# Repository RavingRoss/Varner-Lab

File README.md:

# Current Projects
## SiPMT revA/B:
Includes work on a PCB upgrade to give inputs for a LASER using pogo-pins to activate the given 8 CH ASIC IC chip. 

---

## Waveforms:
Performed testing using dummy data taken from the TOP boardstack in the lab, the waveforms are evenly distributed and plotted.

---

## TOP-BS:
Data taken from the TOP boardstack in Varner lab, testing the 64 SiPM PCB using PCIE40 and KLM VME at UH. Includes advanced version of waveforms parsing script and BS cooling plate upgrades. 

---

## HLS4ML:
This is a project from PHYS 476L which uses the Nexys Video FPGA board for implementation. A keras NN model takes waveform data and predicts the distribution using the mean, sigma, pedestal, and height of the event. This model is then put onto the FPGA by converting it to C using hls4ml. Vitis-HLS is then used to make a Vivado project to implement onto the FPGA.

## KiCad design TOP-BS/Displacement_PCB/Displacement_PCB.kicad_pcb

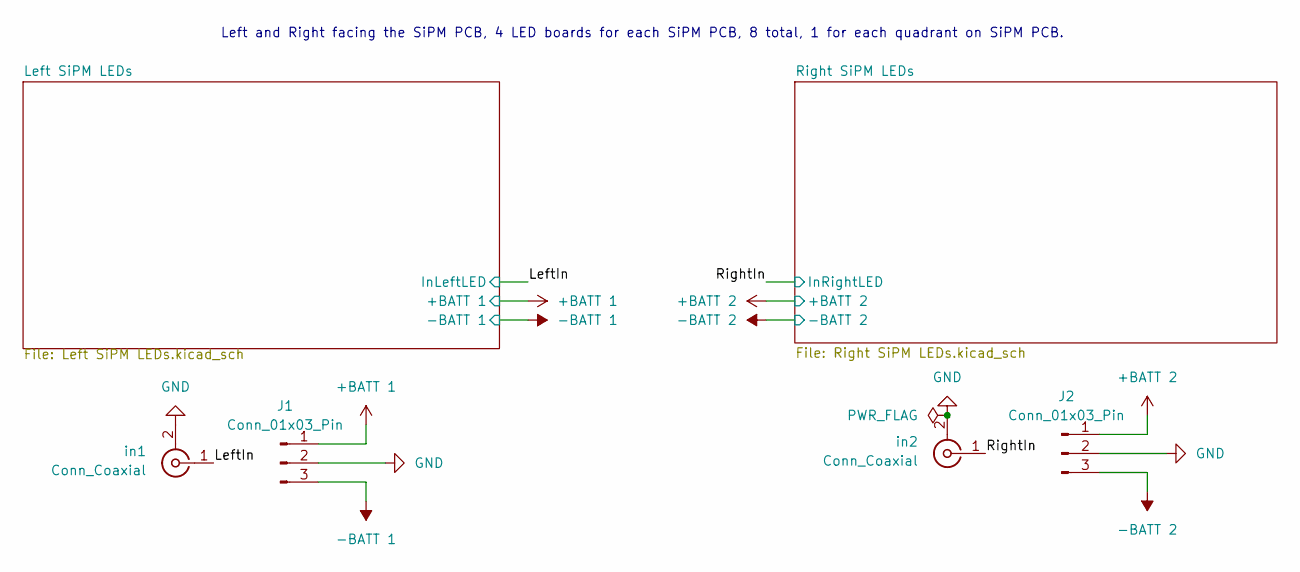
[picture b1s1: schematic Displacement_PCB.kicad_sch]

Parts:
J1, J2: Conn_01x03_Pin; molex-mini-fit-jr-3pos-right-angle-or-16AWG
in1, in2: Conn_Coaxial; MMCX_Molex_73415-1471_Vertical

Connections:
+BATT 1: J1.1; also elsewhere on the board
+BATT 2: J2.1; also elsewhere on the board
-BATT 1: J1.3; also elsewhere on the board
-BATT 2: J2.3; also elsewhere on the board
/LeftIn: in1.1 (In); also elsewhere on the board
/RightIn: in2.1 (In); also elsewhere on the board
GND: J1.2, J2.2, in1.2 (Ext), in2.2 (Ext); also elsewhere on the board

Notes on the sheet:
Left and Right facing the SiPM PCB, 4 LED boards for each SiPM PCB, 8 total, 1 for each quadrant on SiPM PCB.

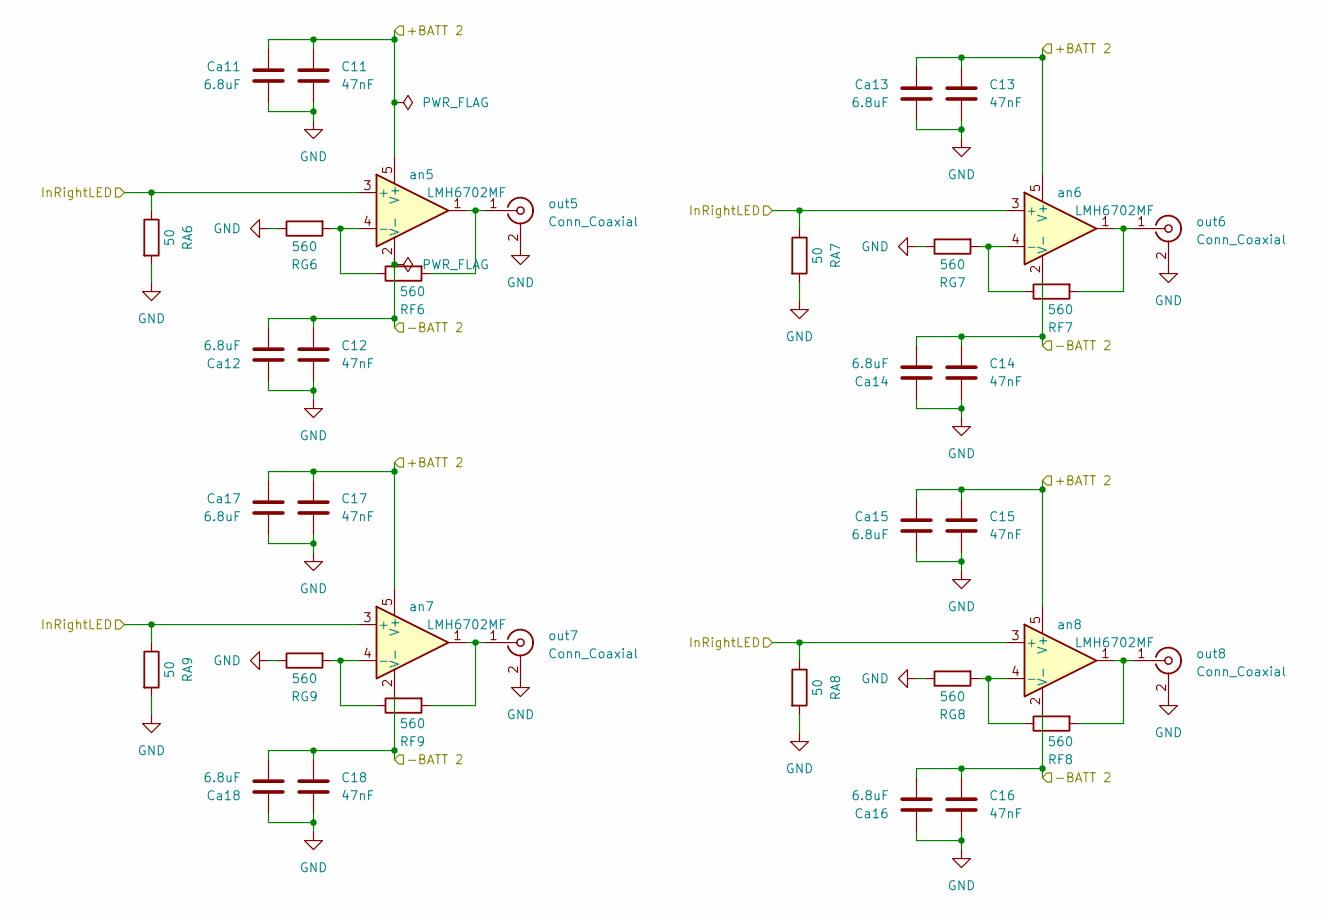
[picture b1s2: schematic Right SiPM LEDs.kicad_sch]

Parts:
C11, C12, C13, C14, C15, C16, C17, C18: 47nF; C_0603_1608Metric_Pad1.08x0.95mm_HandSolder
Ca11, Ca12, Ca13, Ca14, Ca15, Ca16, Ca17, Ca18: 6.8uF; C_0805_2012Metric_Pad1.18x1.45mm_HandSolder
RA6, RA7, RA8, RA9: 50; R_0805_2012Metric_Pad1.20x1.40mm_HandSolder
RF6, RF7, RF8, RF9: 560; R_0603_1608Metric_Pad0.98x0.95mm_HandSolder
RG6, RG7, RG8, RG9: 560; R_0603_1608Metric_Pad0.98x0.95mm_HandSolder
an5, an6, an7, an8: LMH6702MF; SOT-23-5
out5, out6, out7, out8: Conn_Coaxial; MMCX_Molex_73415-1471_Vertical

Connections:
+BATT 2: C11.2, C13.2, C15.2, C17.2, Ca11.1, Ca13.1, Ca15.1, Ca17.1, an5.5 (V+), an6.5 (V+), an7.5 (V+), an8.5 (V+); also elsewhere on the board
-BATT 2: C12.1, C14.1, C16.1, C18.1, Ca12.2, Ca14.2, Ca16.2, Ca18.2, an5.2 (V-), an6.2 (V-), an7.2 (V-), an8.2 (V-); also elsewhere on the board
/RightIn: RA6.1, RA7.1, RA8.1, RA9.1, an5.3 (+), an6.3 (+), an7.3 (+), an8.3 (+); also elsewhere on the board
GND: C11.1, C12.2, C13.1, C14.2, C15.1, C16.2, C17.1, C18.2, Ca11.2, Ca12.1, Ca13.2, Ca14.1, Ca15.2, Ca16.1, Ca17.2, Ca18.1, RA6.2, RA7.2, RA8.2, RA9.2, RG6.1, RG7.1, RG8.1, RG9.1, out5.2 (Ext), out6.2 (Ext), out7.2 (Ext), out8.2 (Ext); also elsewhere on the board
unnamed: RF6.1, RG6.2, an5.4 (-)
unnamed: RF7.1, RG7.2, an6.4 (-)
unnamed: RF9.1, RG9.2, an7.4 (-)
unnamed: RF8.1, RG8.2, an8.4 (-)
unnamed: RF6.2, an5.1, out5.1 (In)
unnamed: RF7.2, an6.1, out6.1 (In)
unnamed: RF9.2, an7.1, out7.1 (In)
unnamed: RF8.2, an8.1, out8.1 (In)

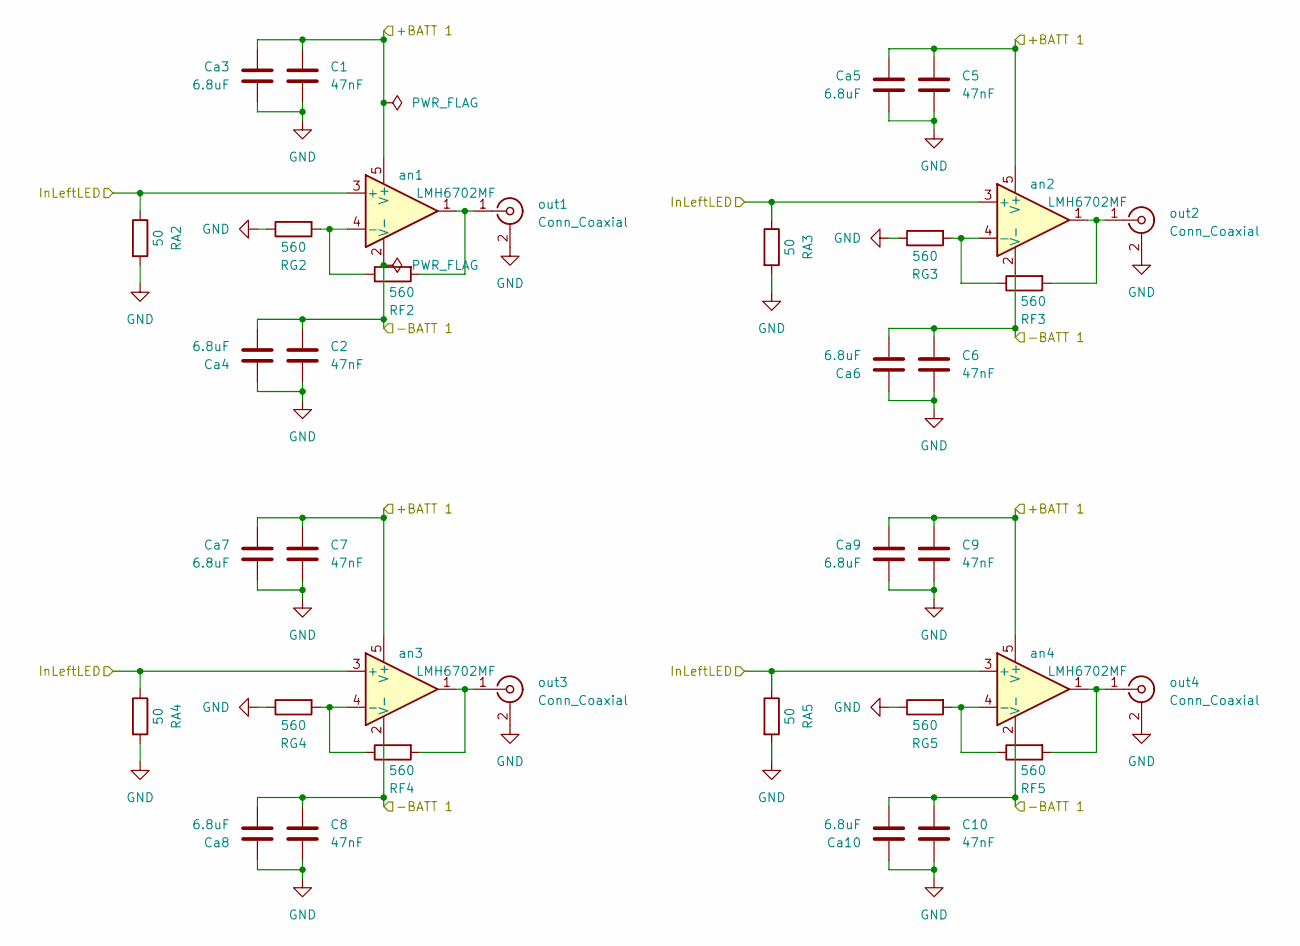
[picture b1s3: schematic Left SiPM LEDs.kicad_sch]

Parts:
C1, C2, C5, C6, C7, C8, C9, C10: 47nF; C_0603_1608Metric_Pad1.08x0.95mm_HandSolder
Ca3, Ca4, Ca5, Ca6, Ca7, Ca8, Ca9, Ca10: 6.8uF; C_0805_2012Metric_Pad1.18x1.45mm_HandSolder
RA2, RA3, RA4, RA5: 50; R_0805_2012Metric_Pad1.20x1.40mm_HandSolder
RF2, RF3, RF4, RF5: 560; R_0603_1608Metric_Pad0.98x0.95mm_HandSolder
RG2, RG3, RG4, RG5: 560; R_0603_1608Metric_Pad0.98x0.95mm_HandSolder
an1, an2, an3, an4: LMH6702MF; SOT-23-5
out1, out2, out3, out4: Conn_Coaxial; MMCX_Molex_73415-1471_Vertical

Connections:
+BATT 1: C1.2, C5.2, C7.2, C9.2, Ca3.1, Ca5.1, Ca7.1, Ca9.1, an1.5 (V+), an2.5 (V+), an3.5 (V+), an4.5 (V+); also elsewhere on the board
-BATT 1: C2.1, C6.1, C8.1, C10.1, Ca4.2, Ca6.2, Ca8.2, Ca10.2, an1.2 (V-), an2.2 (V-), an3.2 (V-), an4.2 (V-); also elsewhere on the board
/LeftIn: RA2.1, RA3.1, RA4.1, RA5.1, an1.3 (+), an2.3 (+), an3.3 (+), an4.3 (+); also elsewhere on the board
GND: C1.1, C2.2, C5.1, C6.2, C7.1, C8.2, C9.1, C10.2, Ca3.2, Ca4.1, Ca5.2, Ca6.1, Ca7.2, Ca8.1, Ca9.2, Ca10.1, RA2.2, RA3.2, RA4.2, RA5.2, RG2.1, RG3.1, RG4.1, RG5.1, out1.2 (Ext), out2.2 (Ext), out3.2 (Ext), out4.2 (Ext); also elsewhere on the board
unnamed: RF2.1, RG2.2, an1.4 (-)
unnamed: RF3.1, RG3.2, an2.4 (-)
unnamed: RF4.1, RG4.2, an3.4 (-)
unnamed: RF5.1, RG5.2, an4.4 (-)
unnamed: RF2.2, an1.1, out1.1 (In)
unnamed: RF3.2, an2.1, out2.1 (In)
unnamed: RF4.2, an3.1, out3.1 (In)
unnamed: RF5.2, an4.1, out4.1 (In)

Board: 2 copper layers, 76 parts (0 on the bottom side), 23 nets, no tracks yet.

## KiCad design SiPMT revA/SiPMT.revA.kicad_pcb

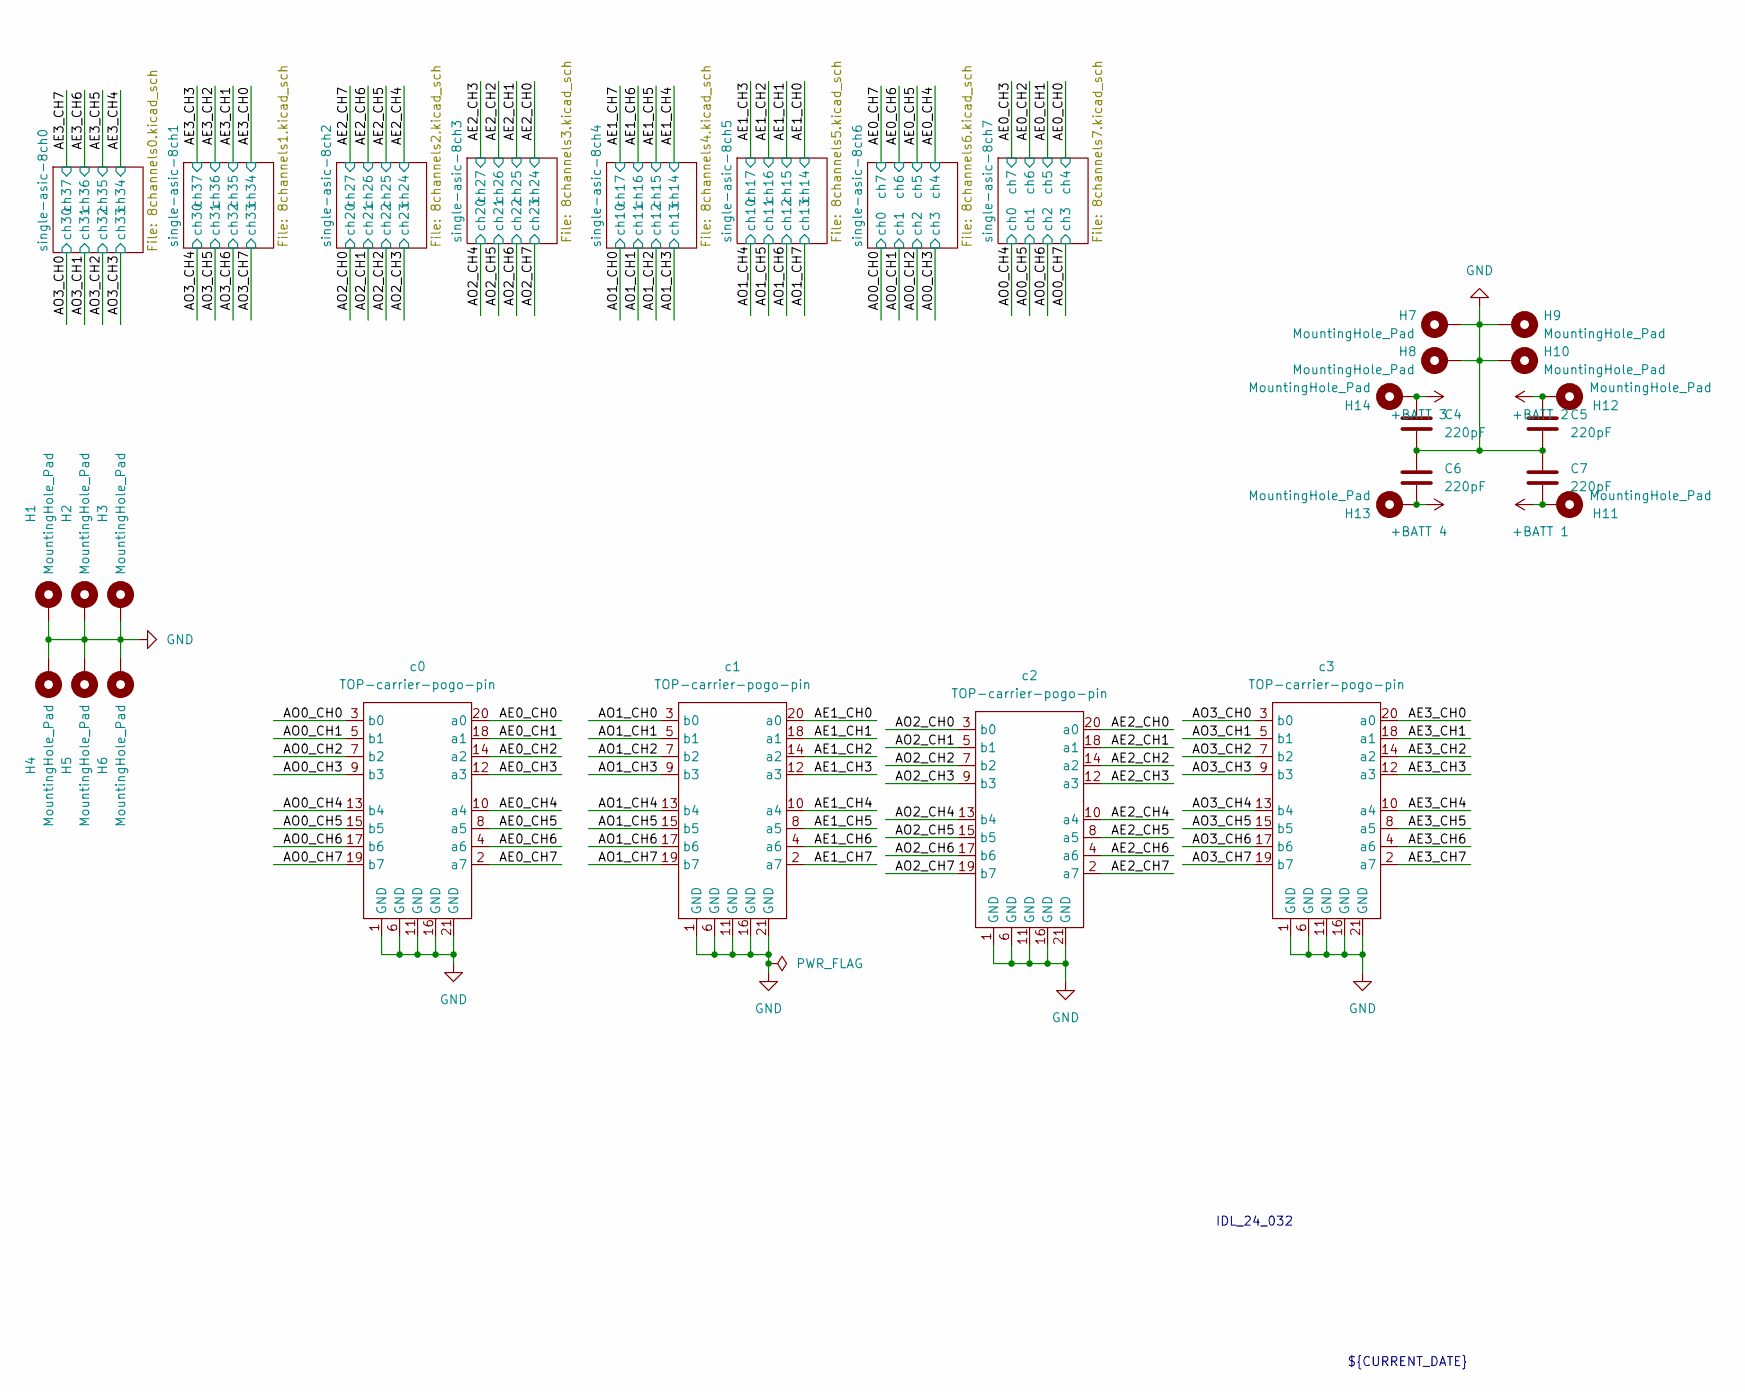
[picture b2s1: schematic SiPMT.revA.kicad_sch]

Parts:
C4, C5, C6, C7: 220pF; C_0603_1608Metric_Pad1.08x0.95mm_HandSolder
H1, H2, H3, H4, H5, H6: MountingHole_Pad; MountingHole_2.5mm_Pad
H7, H8, H9, H10, H11, H12, H13, H14: MountingHole_Pad; MountingHole_1.5mm_Pad
c0, c1, c2, c3: TOP-carrier-pogo-pin

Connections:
+BATT 1: C7.2, H11.1; also elsewhere on the board
+BATT 2: C5.1, H12.1; also elsewhere on the board
+BATT 3: C4.1, H14.1; also elsewhere on the board
+BATT 4: C6.2, H13.1; also elsewhere on the board
/AE0_CH0: c0.20 (a0); also elsewhere on the board
/AE0_CH1: c0.18 (a1); also elsewhere on the board
/AE0_CH2: c0.14 (a2); also elsewhere on the board
/AE0_CH3: c0.12 (a3); also elsewhere on the board
/AE0_CH4: c0.10 (a4); also elsewhere on the board
/AE0_CH5: c0.8 (a5); also elsewhere on the board
/AE0_CH6: c0.4 (a6); also elsewhere on the board
/AE0_CH7: c0.2 (a7); also elsewhere on the board
/AE1_CH0: c1.20 (a0); also elsewhere on the board
/AE1_CH1: c1.18 (a1); also elsewhere on the board
/AE1_CH2: c1.14 (a2); also elsewhere on the board
/AE1_CH3: c1.12 (a3); also elsewhere on the board
/AE1_CH4: c1.10 (a4); also elsewhere on the board
/AE1_CH5: c1.8 (a5); also elsewhere on the board
/AE1_CH6: c1.4 (a6); also elsewhere on the board
/AE1_CH7: c1.2 (a7); also elsewhere on the board
/AE2_CH0: c2.20 (a0); also elsewhere on the board
/AE2_CH1: c2.18 (a1); also elsewhere on the board
/AE2_CH2: c2.14 (a2); also elsewhere on the board
/AE2_CH3: c2.12 (a3); also elsewhere on the board
/AE2_CH4: c2.10 (a4); also elsewhere on the board
/AE2_CH5: c2.8 (a5); also elsewhere on the board
/AE2_CH6: c2.4 (a6); also elsewhere on the board
/AE2_CH7: c2.2 (a7); also elsewhere on the board
/AE3_CH0: c3.20 (a0); also elsewhere on the board
/AE3_CH1: c3.18 (a1); also elsewhere on the board
/AE3_CH2: c3.14 (a2); also elsewhere on the board
/AE3_CH3: c3.12 (a3); also elsewhere on the board
/AE3_CH4: c3.10 (a4); also elsewhere on the board
/AE3_CH5: c3.8 (a5); also elsewhere on the board
/AE3_CH6: c3.4 (a6); also elsewhere on the board
/AE3_CH7: c3.2 (a7); also elsewhere on the board
/AO0_CH0: c0.3 (b0); also elsewhere on the board
/AO0_CH1: c0.5 (b1); also elsewhere on the board
/AO0_CH2: c0.7 (b2); also elsewhere on the board
/AO0_CH3: c0.9 (b3); also elsewhere on the board
/AO0_CH4: c0.13 (b4); also elsewhere on the board
/AO0_CH5: c0.15 (b5); also elsewhere on the board
/AO0_CH6: c0.17 (b6); also elsewhere on the board
/AO0_CH7: c0.19 (b7); also elsewhere on the board
/AO1_CH0: c1.3 (b0); also elsewhere on the board
/AO1_CH1: c1.5 (b1); also elsewhere on the board
/AO1_CH2: c1.7 (b2); also elsewhere on the board
/AO1_CH3: c1.9 (b3); also elsewhere on the board
/AO1_CH4: c1.13 (b4); also elsewhere on the board
/AO1_CH5: c1.15 (b5); also elsewhere on the board
/AO1_CH6: c1.17 (b6); also elsewhere on the board
/AO1_CH7: c1.19 (b7); also elsewhere on the board
/AO2_CH0: c2.3 (b0); also elsewhere on the board
/AO2_CH1: c2.5 (b1); also elsewhere on the board
/AO2_CH2: c2.7 (b2); also elsewhere on the board
/AO2_CH3: c2.9 (b3); also elsewhere on the board
/AO2_CH4: c2.13 (b4); also elsewhere on the board
/AO2_CH5: c2.15 (b5); also elsewhere on the board
/AO2_CH6: c2.17 (b6); also elsewhere on the board
/AO2_CH7: c2.19 (b7); also elsewhere on the board
/AO3_CH0: c3.3 (b0); also elsewhere on the board
/AO3_CH1: c3.5 (b1); also elsewhere on the board
/AO3_CH2: c3.7 (b2); also elsewhere on the board
/AO3_CH3: c3.9 (b3); also elsewhere on the board
/AO3_CH4: c3.13 (b4); also elsewhere on the board
/AO3_CH5: c3.15 (b5); also elsewhere on the board
/AO3_CH6: c3.17 (b6); also elsewhere on the board
/AO3_CH7: c3.19 (b7); also elsewhere on the board
GND: C4.2, C5.2, C6.1, C7.1, H1.1, H2.1, H3.1, H4.1, H5.1, H6.1, H7.1, H8.1, H9.1, H10.1, c0.1 (GND), c0.6 (GND), c0.11 (GND), c0.16 (GND), c0.21 (GND), c1.1 (GND), c1.6 (GND), c1.11 (GND), c1.16 (GND), c1.21 (GND), c2.1 (GND), c2.6 (GND), c2.11 (GND), c2.16 (GND), c2.21 (GND), c3.1 (GND), c3.6 (GND), c3.11 (GND), c3.16 (GND), c3.21 (GND)

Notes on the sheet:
${CURRENT_DATE}
IDL_24_032

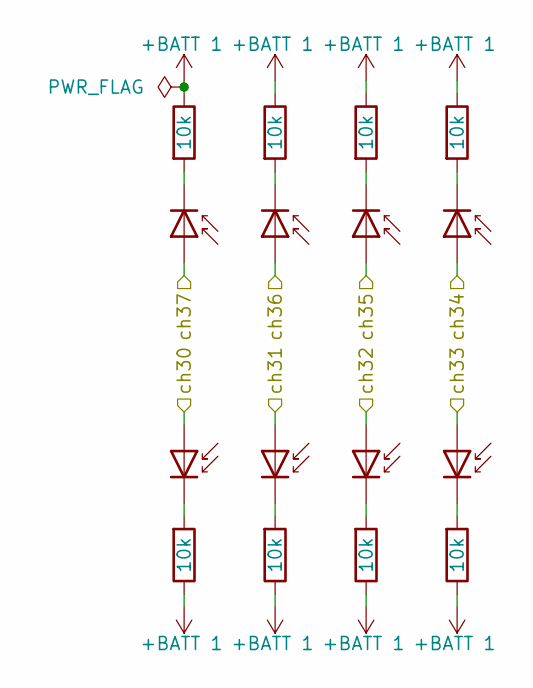
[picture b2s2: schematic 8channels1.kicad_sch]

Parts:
D1, D2, D3, D4, D5, D6, D8, D9: D_SiPM; Hamamatsu_S10362-11-100P-plus
R1, R2, R3, R4, R5, R6, R8, R9: 10k; 0603

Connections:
+BATT 1: R1.1, R2.1, R3.1, R4.1, R5.1, R6.1, R8.1, R9.1; also elsewhere on the board
/AE3_CH0: D8.2 (A); also elsewhere on the board
/AE3_CH1: D5.2 (A); also elsewhere on the board
/AE3_CH2: D3.2 (A); also elsewhere on the board
/AE3_CH3: D1.2 (A); also elsewhere on the board
/AO3_CH4: D2.2 (A); also elsewhere on the board
/AO3_CH5: D4.2 (A); also elsewhere on the board
/AO3_CH6: D6.2 (A); also elsewhere on the board
/AO3_CH7: D9.2 (A); also elsewhere on the board
unnamed: D1.1 (K), R1.2
unnamed: D2.1 (K), R2.2
unnamed: D3.1 (K), R3.2
unnamed: D4.1 (K), R4.2
unnamed: D5.1 (K), R5.2
unnamed: D6.1 (K), R6.2
unnamed: D8.1 (K), R8.2
unnamed: D9.1 (K), R9.2

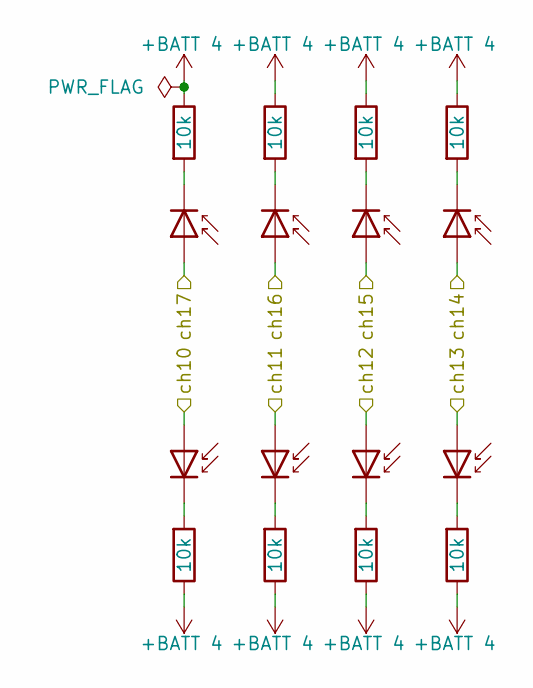
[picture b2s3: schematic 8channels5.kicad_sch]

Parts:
D41, D42, D43, D44, D45, D46, D47, D48: D_SiPM; Hamamatsu_S10362-11-100P-plus
R41, R42, R43, R44, R45, R46, R47, R48: 10k; 0603

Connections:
+BATT 4: R41.1, R42.1, R43.1, R44.1, R45.1, R46.1, R47.1, R48.1; also elsewhere on the board
/AE1_CH0: D47.2 (A); also elsewhere on the board
/AE1_CH1: D45.2 (A); also elsewhere on the board
/AE1_CH2: D43.2 (A); also elsewhere on the board
/AE1_CH3: D41.2 (A); also elsewhere on the board
/AO1_CH4: D42.2 (A); also elsewhere on the board
/AO1_CH5: D44.2 (A); also elsewhere on the board
/AO1_CH6: D46.2 (A); also elsewhere on the board
/AO1_CH7: D48.2 (A); also elsewhere on the board
unnamed: D41.1 (K), R41.2
unnamed: D42.1 (K), R42.2
unnamed: D43.1 (K), R43.2
unnamed: D44.1 (K), R44.2
unnamed: D45.1 (K), R45.2
unnamed: D46.1 (K), R46.2
unnamed: D47.1 (K), R47.2
unnamed: D48.1 (K), R48.2

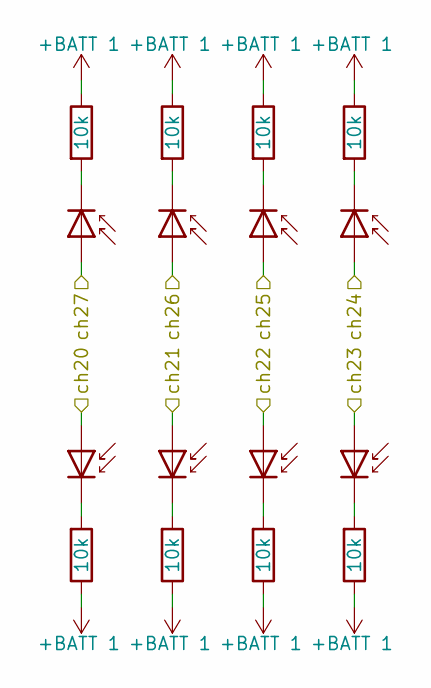
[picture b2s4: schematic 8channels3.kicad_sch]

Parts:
D25, D26, D27, D28, D29, D30, D31, D32: D_SiPM; Hamamatsu_S10362-11-100P-plus
R25, R26, R27, R28, R29, R30, R31, R32: 10k; 0603

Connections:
+BATT 1: R25.1, R26.1, R27.1, R28.1, R29.1, R30.1, R31.1, R32.1; also elsewhere on the board
/AE2_CH0: D31.2 (A); also elsewhere on the board
/AE2_CH1: D29.2 (A); also elsewhere on the board
/AE2_CH2: D27.2 (A); also elsewhere on the board
/AE2_CH3: D25.2 (A); also elsewhere on the board
/AO2_CH4: D26.2 (A); also elsewhere on the board
/AO2_CH5: D28.2 (A); also elsewhere on the board
/AO2_CH6: D30.2 (A); also elsewhere on the board
/AO2_CH7: D32.2 (A); also elsewhere on the board
unnamed: D25.1 (K), R25.2
unnamed: D26.1 (K), R26.2
unnamed: D27.1 (K), R27.2
unnamed: D28.1 (K), R28.2
unnamed: D29.1 (K), R29.2
unnamed: D30.1 (K), R30.2
unnamed: D31.1 (K), R31.2
unnamed: D32.1 (K), R32.2

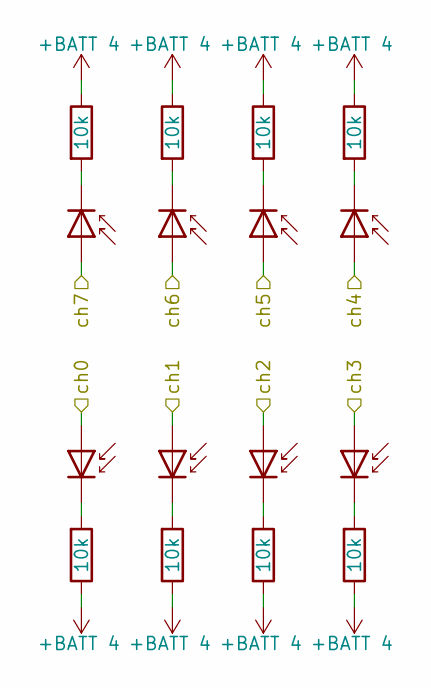
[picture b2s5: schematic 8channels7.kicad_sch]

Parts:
D57, D58, D59, D60, D61, D62, D63, D64: D_SiPM; Hamamatsu_S10362-11-100P-plus
R57, R58, R59, R60, R61, R62, R63, R64: 10k; 0603

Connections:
+BATT 4: R57.1, R58.1, R59.1, R60.1, R61.1, R62.1, R63.1, R64.1; also elsewhere on the board
/AE0_CH0: D63.2 (A); also elsewhere on the board
/AE0_CH1: D61.2 (A); also elsewhere on the board
/AE0_CH2: D59.2 (A); also elsewhere on the board
/AE0_CH3: D57.2 (A); also elsewhere on the board
/AO0_CH4: D58.2 (A); also elsewhere on the board
/AO0_CH5: D60.2 (A); also elsewhere on the board
/AO0_CH6: D62.2 (A); also elsewhere on the board
/AO0_CH7: D64.2 (A); also elsewhere on the board
unnamed: D57.1 (K), R57.2
unnamed: D58.1 (K), R58.2
unnamed: D59.1 (K), R59.2
unnamed: D60.1 (K), R60.2
unnamed: D61.1 (K), R61.2
unnamed: D62.1 (K), R62.2
unnamed: D63.1 (K), R63.2
unnamed: D64.1 (K), R64.2

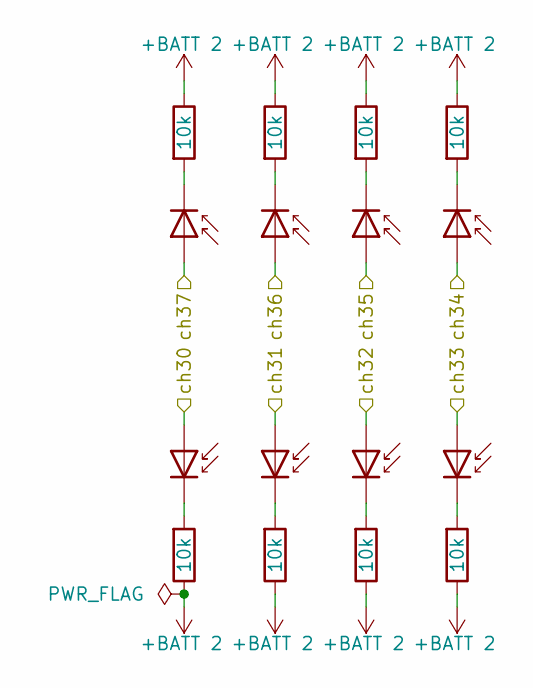
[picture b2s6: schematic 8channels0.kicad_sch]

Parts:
D7, D15, D17, D18, D19, D20, D21, D22: D_SiPM; Hamamatsu_S10362-11-100P-plus
R7, R15, R17, R18, R19, R20, R21, R22: 10k; 0603

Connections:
+BATT 2: R7.1, R15.1, R17.1, R18.1, R19.1, R20.1, R21.1, R22.1; also elsewhere on the board
/AE3_CH4: D22.2 (A); also elsewhere on the board
/AE3_CH5: D21.2 (A); also elsewhere on the board
/AE3_CH6: D19.2 (A); also elsewhere on the board
/AE3_CH7: D18.2 (A); also elsewhere on the board
/AO3_CH0: D7.2 (A); also elsewhere on the board
/AO3_CH1: D20.2 (A); also elsewhere on the board
/AO3_CH2: D15.2 (A); also elsewhere on the board
/AO3_CH3: D17.2 (A); also elsewhere on the board
unnamed: D7.1 (K), R7.2
unnamed: D15.1 (K), R15.2
unnamed: D17.1 (K), R17.2
unnamed: D18.1 (K), R18.2
unnamed: D19.1 (K), R19.2
unnamed: D20.1 (K), R20.2
unnamed: D21.1 (K), R21.2
unnamed: D22.1 (K), R22.2

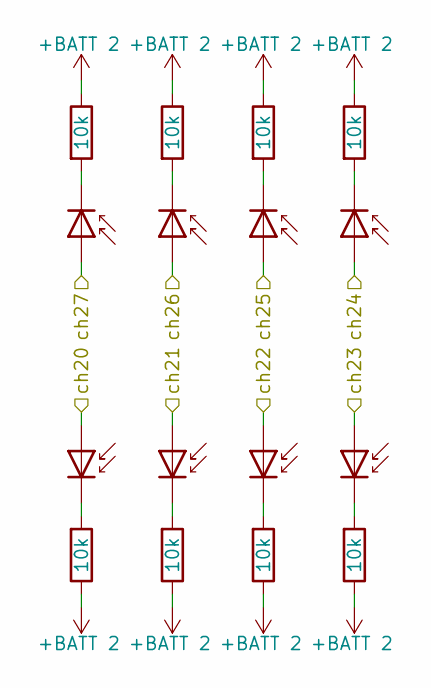
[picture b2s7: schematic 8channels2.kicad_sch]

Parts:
D10, D11, D12, D13, D14, D16, D23, D24: D_SiPM; Hamamatsu_S10362-11-100P-plus
R10, R11, R12, R13, R14, R16, R23, R24: 10k; 0603

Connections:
+BATT 2: R10.1, R11.1, R12.1, R13.1, R14.1, R16.1, R23.1, R24.1; also elsewhere on the board
/AE2_CH4: D23.2 (A); also elsewhere on the board
/AE2_CH5: D14.2 (A); also elsewhere on the board
/AE2_CH6: D12.2 (A); also elsewhere on the board
/AE2_CH7: D10.2 (A); also elsewhere on the board
/AO2_CH0: D11.2 (A); also elsewhere on the board
/AO2_CH1: D13.2 (A); also elsewhere on the board
/AO2_CH2: D16.2 (A); also elsewhere on the board
/AO2_CH3: D24.2 (A); also elsewhere on the board
unnamed: D10.1 (K), R10.2
unnamed: D11.1 (K), R11.2
unnamed: D12.1 (K), R12.2
unnamed: D13.1 (K), R13.2
unnamed: D14.1 (K), R14.2
unnamed: D16.1 (K), R16.2
unnamed: D23.1 (K), R23.2
unnamed: D24.1 (K), R24.2

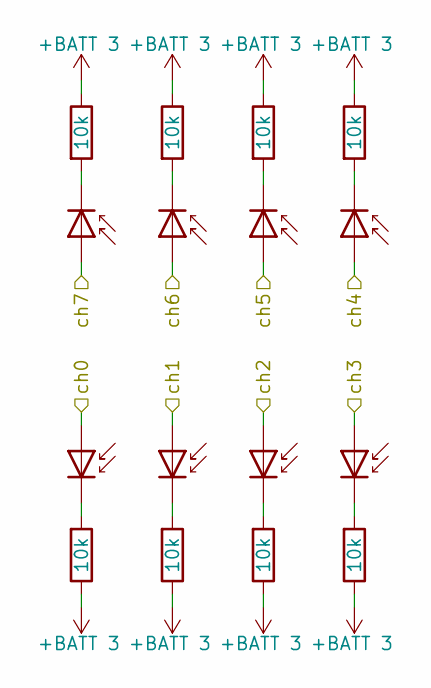
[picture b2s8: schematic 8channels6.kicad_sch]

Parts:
D49, D50, D51, D52, D53, D54, D55, D56: D_SiPM; Hamamatsu_S10362-11-100P-plus
R49, R50, R51, R52, R53, R54, R55, R56: 10k; 0603

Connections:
+BATT 3: R49.1, R50.1, R51.1, R52.1, R53.1, R54.1, R55.1, R56.1; also elsewhere on the board
/AE0_CH4: D55.2 (A); also elsewhere on the board
/AE0_CH5: D53.2 (A); also elsewhere on the board
/AE0_CH6: D51.2 (A); also elsewhere on the board
/AE0_CH7: D49.2 (A); also elsewhere on the board
/AO0_CH0: D50.2 (A); also elsewhere on the board
/AO0_CH1: D52.2 (A); also elsewhere on the board
/AO0_CH2: D54.2 (A); also elsewhere on the board
/AO0_CH3: D56.2 (A); also elsewhere on the board
unnamed: D49.1 (K), R49.2
unnamed: D50.1 (K), R50.2
unnamed: D51.1 (K), R51.2
unnamed: D52.1 (K), R52.2
unnamed: D53.1 (K), R53.2
unnamed: D54.1 (K), R54.2
unnamed: D55.1 (K), R55.2
unnamed: D56.1 (K), R56.2

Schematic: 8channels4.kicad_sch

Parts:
D33, D34, D35, D36, D37, D38, D39, D40: D_SiPM; Hamamatsu_S10362-11-100P-plus
R33, R34, R35, R36, R37, R38, R39, R40: 10k; 0603

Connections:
+BATT 3: R33.1, R34.1, R35.1, R36.1, R37.1, R38.1, R39.1, R40.1; also elsewhere on the board
/AE1_CH4: D39.2 (A); also elsewhere on the board
/AE1_CH5: D37.2 (A); also elsewhere on the board
/AE1_CH6: D35.2 (A); also elsewhere on the board
/AE1_CH7: D33.2 (A); also elsewhere on the board
/AO1_CH0: D34.2 (A); also elsewhere on the board
/AO1_CH1: D36.2 (A); also elsewhere on the board
/AO1_CH2: D38.2 (A); also elsewhere on the board
/AO1_CH3: D40.2 (A); also elsewhere on the board
unnamed: D33.1 (K), R33.2
unnamed: D34.1 (K), R34.2
unnamed: D35.1 (K), R35.2
unnamed: D36.1 (K), R36.2
unnamed: D37.1 (K), R37.2
unnamed: D38.1 (K), R38.2
unnamed: D39.1 (K), R39.2
unnamed: D40.1 (K), R40.2

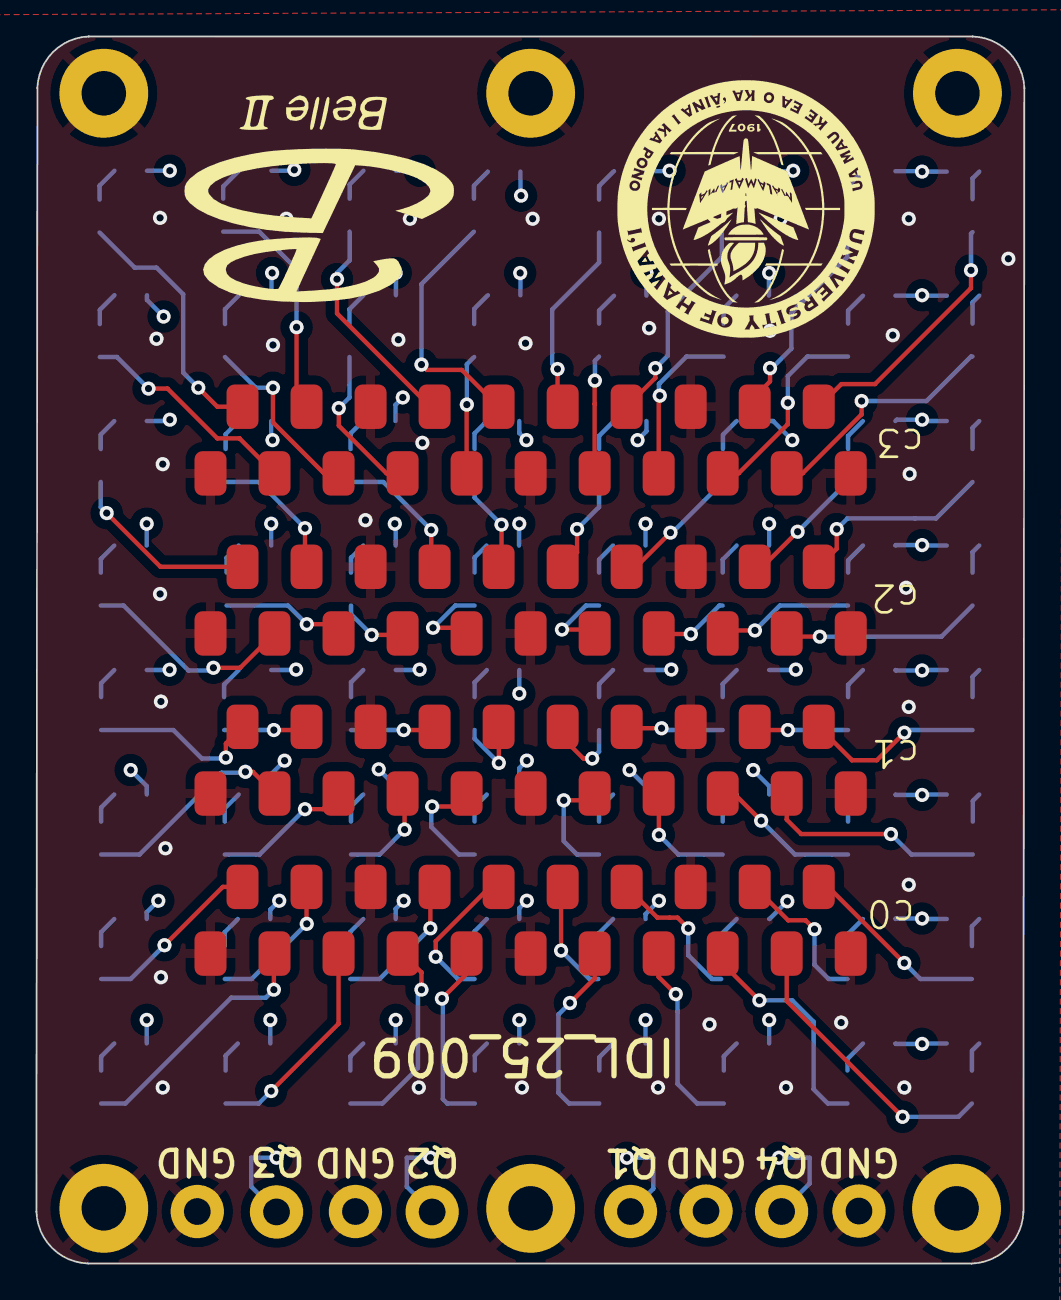
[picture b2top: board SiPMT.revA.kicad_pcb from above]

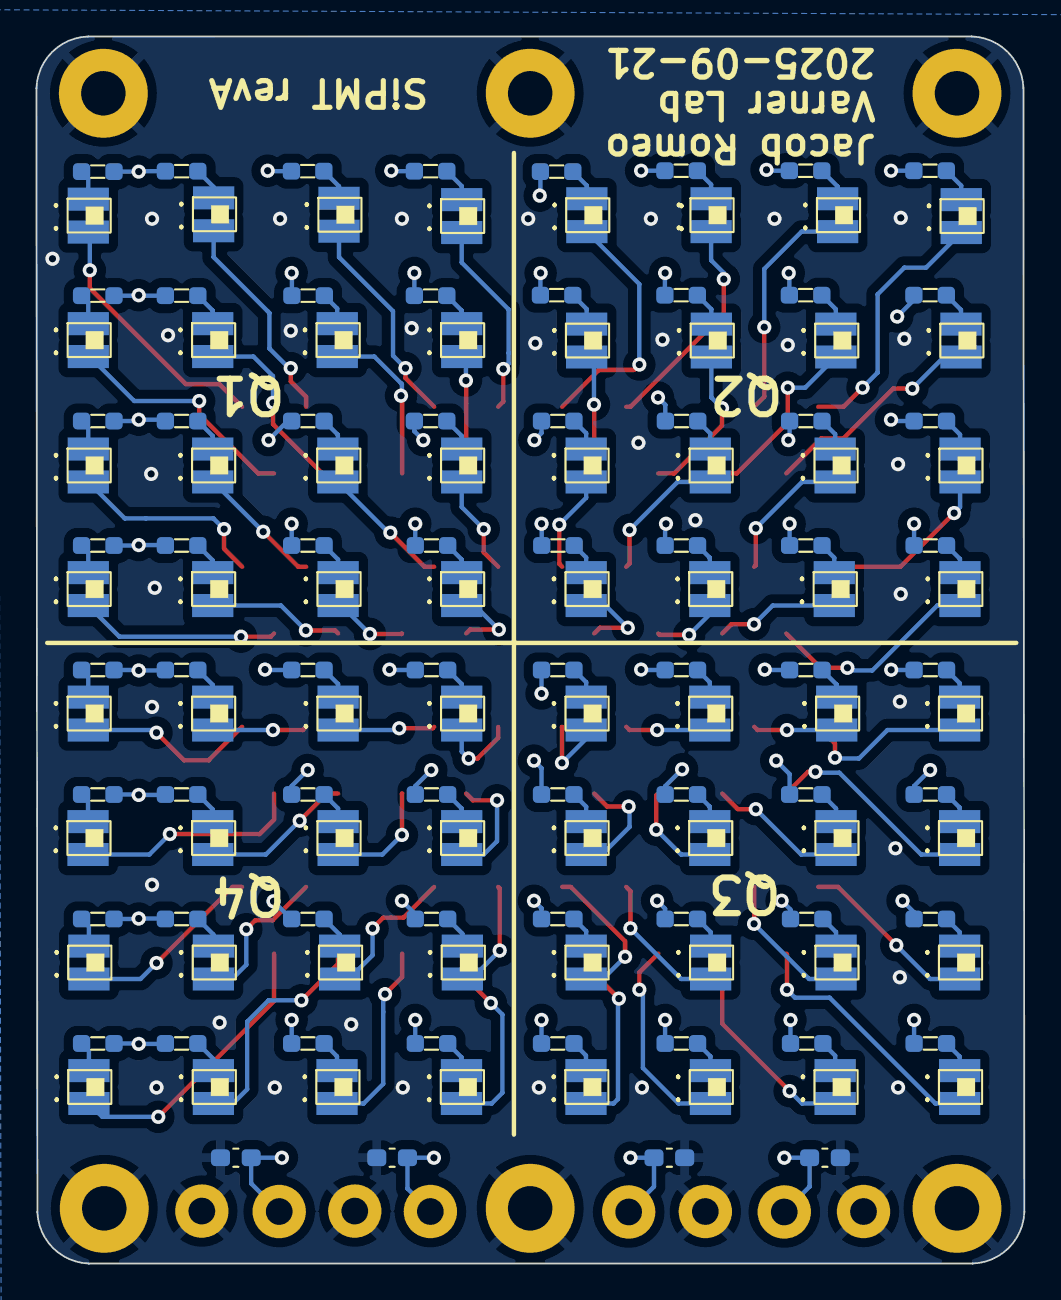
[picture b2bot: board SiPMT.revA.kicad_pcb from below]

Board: 4 copper layers, 55.6 x 69.0 mm, 150 parts (132 on the bottom side), 133 nets.

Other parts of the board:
Q1, Q2, Q3, Q4: MountingHole_Pad; MountingHole_1.5mm_Pad

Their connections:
+BATT 1: Q1.1; also elsewhere on the board
+BATT 2: Q2.1; also elsewhere on the board
+BATT 3: Q3.1; also elsewhere on the board
+BATT 4: Q4.1; also elsewhere on the board
